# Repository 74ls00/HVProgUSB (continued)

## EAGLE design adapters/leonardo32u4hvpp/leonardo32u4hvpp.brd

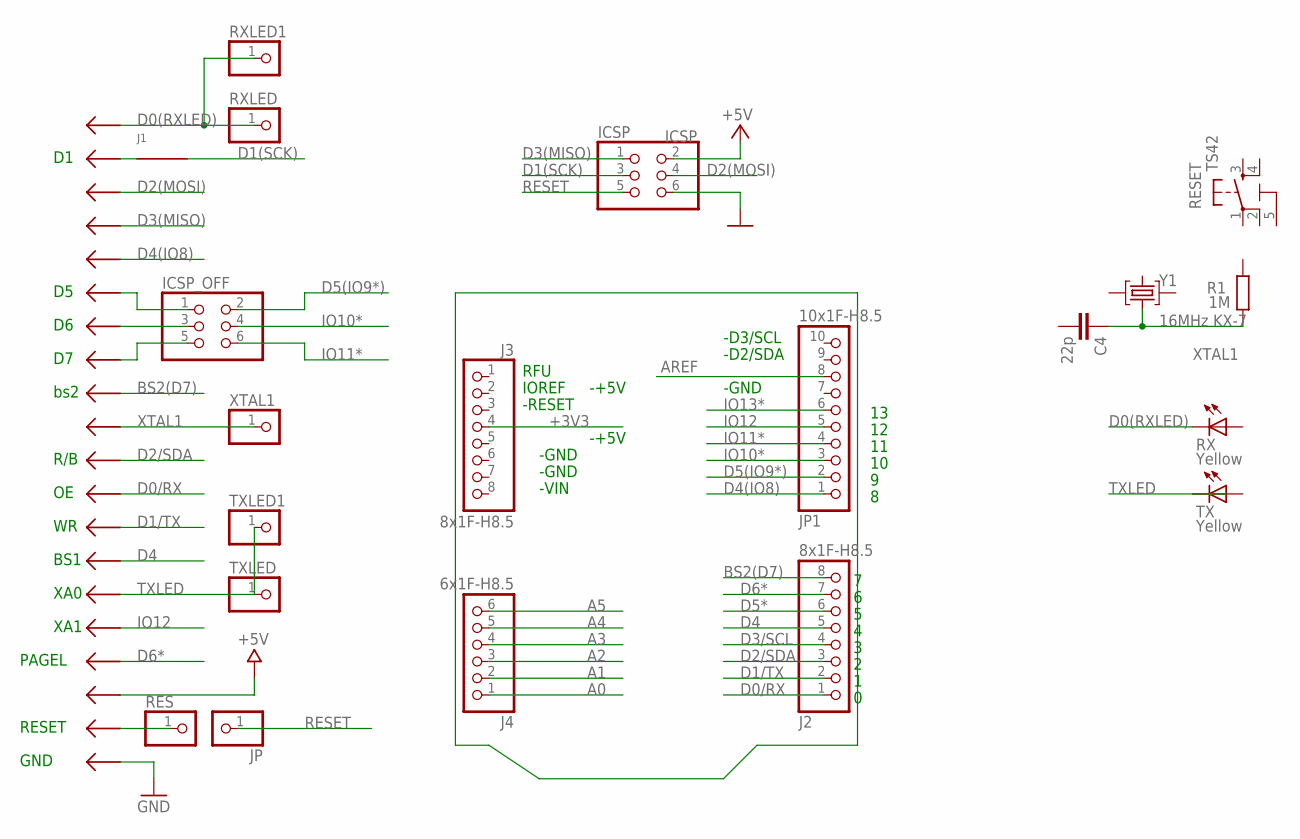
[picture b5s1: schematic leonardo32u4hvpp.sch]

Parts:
C4: 22p; C0603-ROUND
ICSP: ICSP; 2X03
ICSP_OFF: PINHD-2X3; 2X03
J1: J; R1206W
J2, J3: 8x1F-H8.5; 1X08
J4: 6x1F-H8.5; 1X06
JP: PINHD-1X1; 1X01
JP1: 10x1F-H8.5; 1X10
R1: 1M; R0603-ROUND
RES: PINHD-1X1; 1X01
RESET: TS42
RX: Yellow; CHIPLED_0805
RXLED, RXLED1: PINHD-1X1; 1X01
TX: Yellow; CHIPLED_0805
TXLED, TXLED1: PINHD-1X1; 1X01
U$2: PROGRAMMER_P_AVR
XTAL1: PINHD-1X1; 1X01
Y1: 16MHz KX-7; CRYSTAL-3.2-2.5

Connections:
5-GND: RESET.5 (5-GND)
+3V3: J3.4
+5V: ICSP.2, U$2.VCC
A0: J4.1
A1: J4.2
A2: J4.3
A3: J4.4
A4: J4.5
A5: J4.6
AREF: JP1.8
BS2(D7): J2.8, U$2.BS2
D0(RXLED): RX.C, RXLED.1, RXLED1.1, U$2.D0
D0/RX: J2.1, U$2.OE
D1(SCK): ICSP.3, J1.1
D1/TX: J2.2, U$2.WR
D2(MOSI): ICSP.4, U$2.D2
D2/SDA: J2.3, U$2.RB
D3(MISO): ICSP.1, U$2.D3
D3/SCL: J2.4
D4: J2.5, U$2.BS1
D4(IO8): JP1.1, U$2.D4
D5(IO9*): ICSP_OFF.2, JP1.2
D5*: J2.6
D6*: J2.7, U$2.PAGEL
GND: ICSP.6, U$2.GND, U$2.GND01 (GND), U$2.GND2 (GND), U$2.GND03 (GND), U$2.GND04 (GND), U$2.GND05 (GND), U$2.GND06 (GND), U$2.GND07 (GND), U$2.GND08 (GND), U$2.GND09 (GND), U$2.GND10 (GND), U$2.GND11 (GND), U$2.GND12 (GND), U$2.GND13 (GND), U$2.GND14 (GND), U$2.GND15 (GND), U$2.GND16 (GND), U$2.GND17 (GND), U$2.GND18 (GND), U$2.GND19 (GND), U$2.GND20 (GND), U$2.GND21 (GND), U$2.GND22 (GND)
IO10*: ICSP_OFF.4, JP1.3
IO11*: ICSP_OFF.6, JP1.4
IO12: JP1.5, U$2.XA1
IO13*: JP1.6
unnamed: J1.2, U$2.D1
unnamed: ICSP_OFF.5, U$2.D7
unnamed: ICSP_OFF.3, U$2.D6
unnamed: ICSP_OFF.1, U$2.D5
unnamed: RES.1, U$2.RESET
RESET: ICSP.5, JP.1
TXLED: TX.C, TXLED.1, TXLED1.1, U$2.XA0
XTAL1: C4.1, R1.1, U$2.XTAL1, XTAL1.1, Y1.1 (C1)

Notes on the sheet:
IOREF
RFU
bs2
R/B
BS1
XA0
XA1
PAGEL
RESET
GND
-D2/SDA
-D3/SCL
-GND
-VIN
-RESET
-+5V

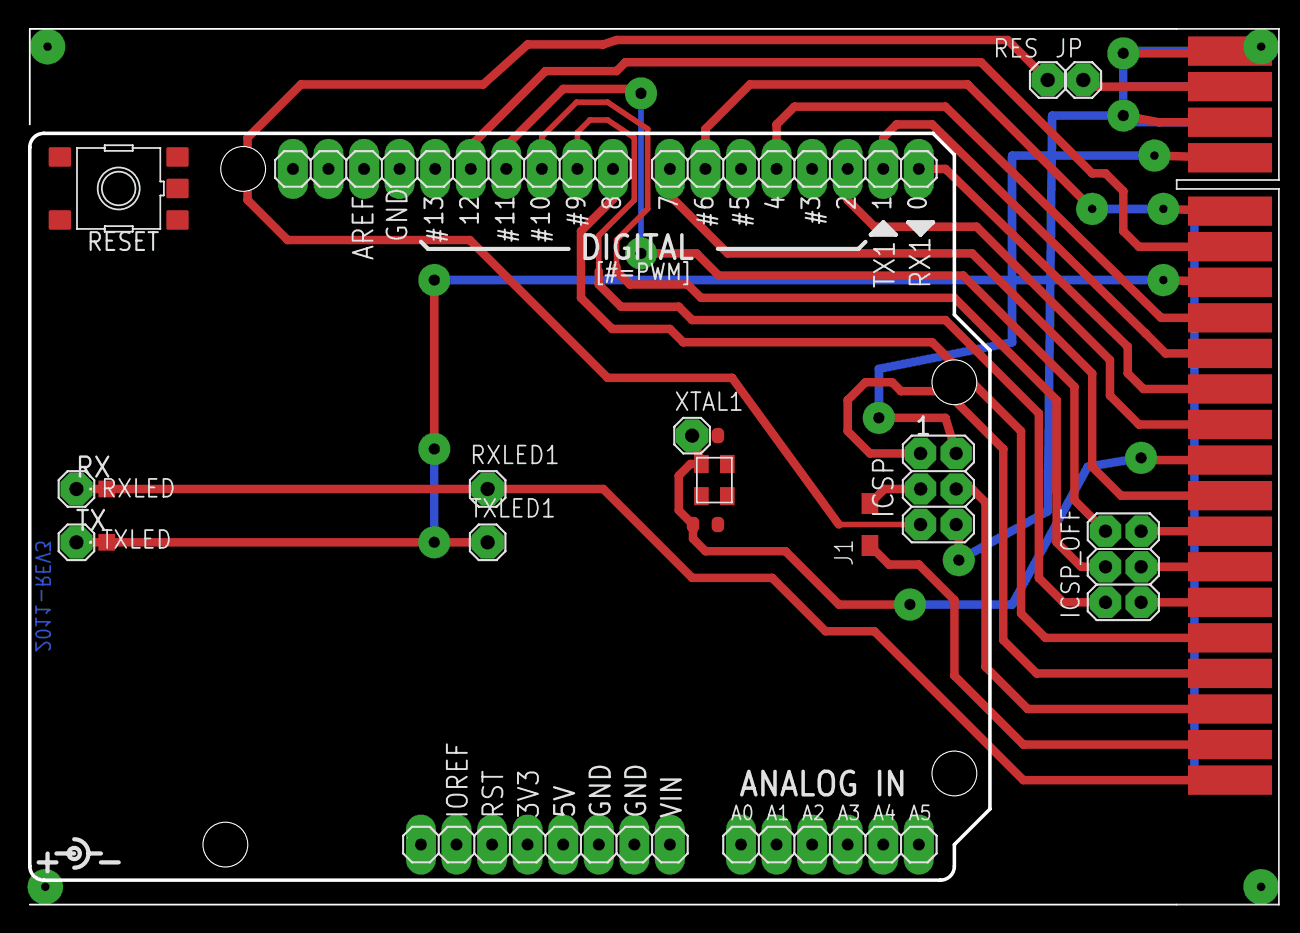
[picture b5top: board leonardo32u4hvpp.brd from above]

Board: 2 copper layers, 68.6 x 53.3 mm, 21 parts (1 on the bottom side), 25 nets.

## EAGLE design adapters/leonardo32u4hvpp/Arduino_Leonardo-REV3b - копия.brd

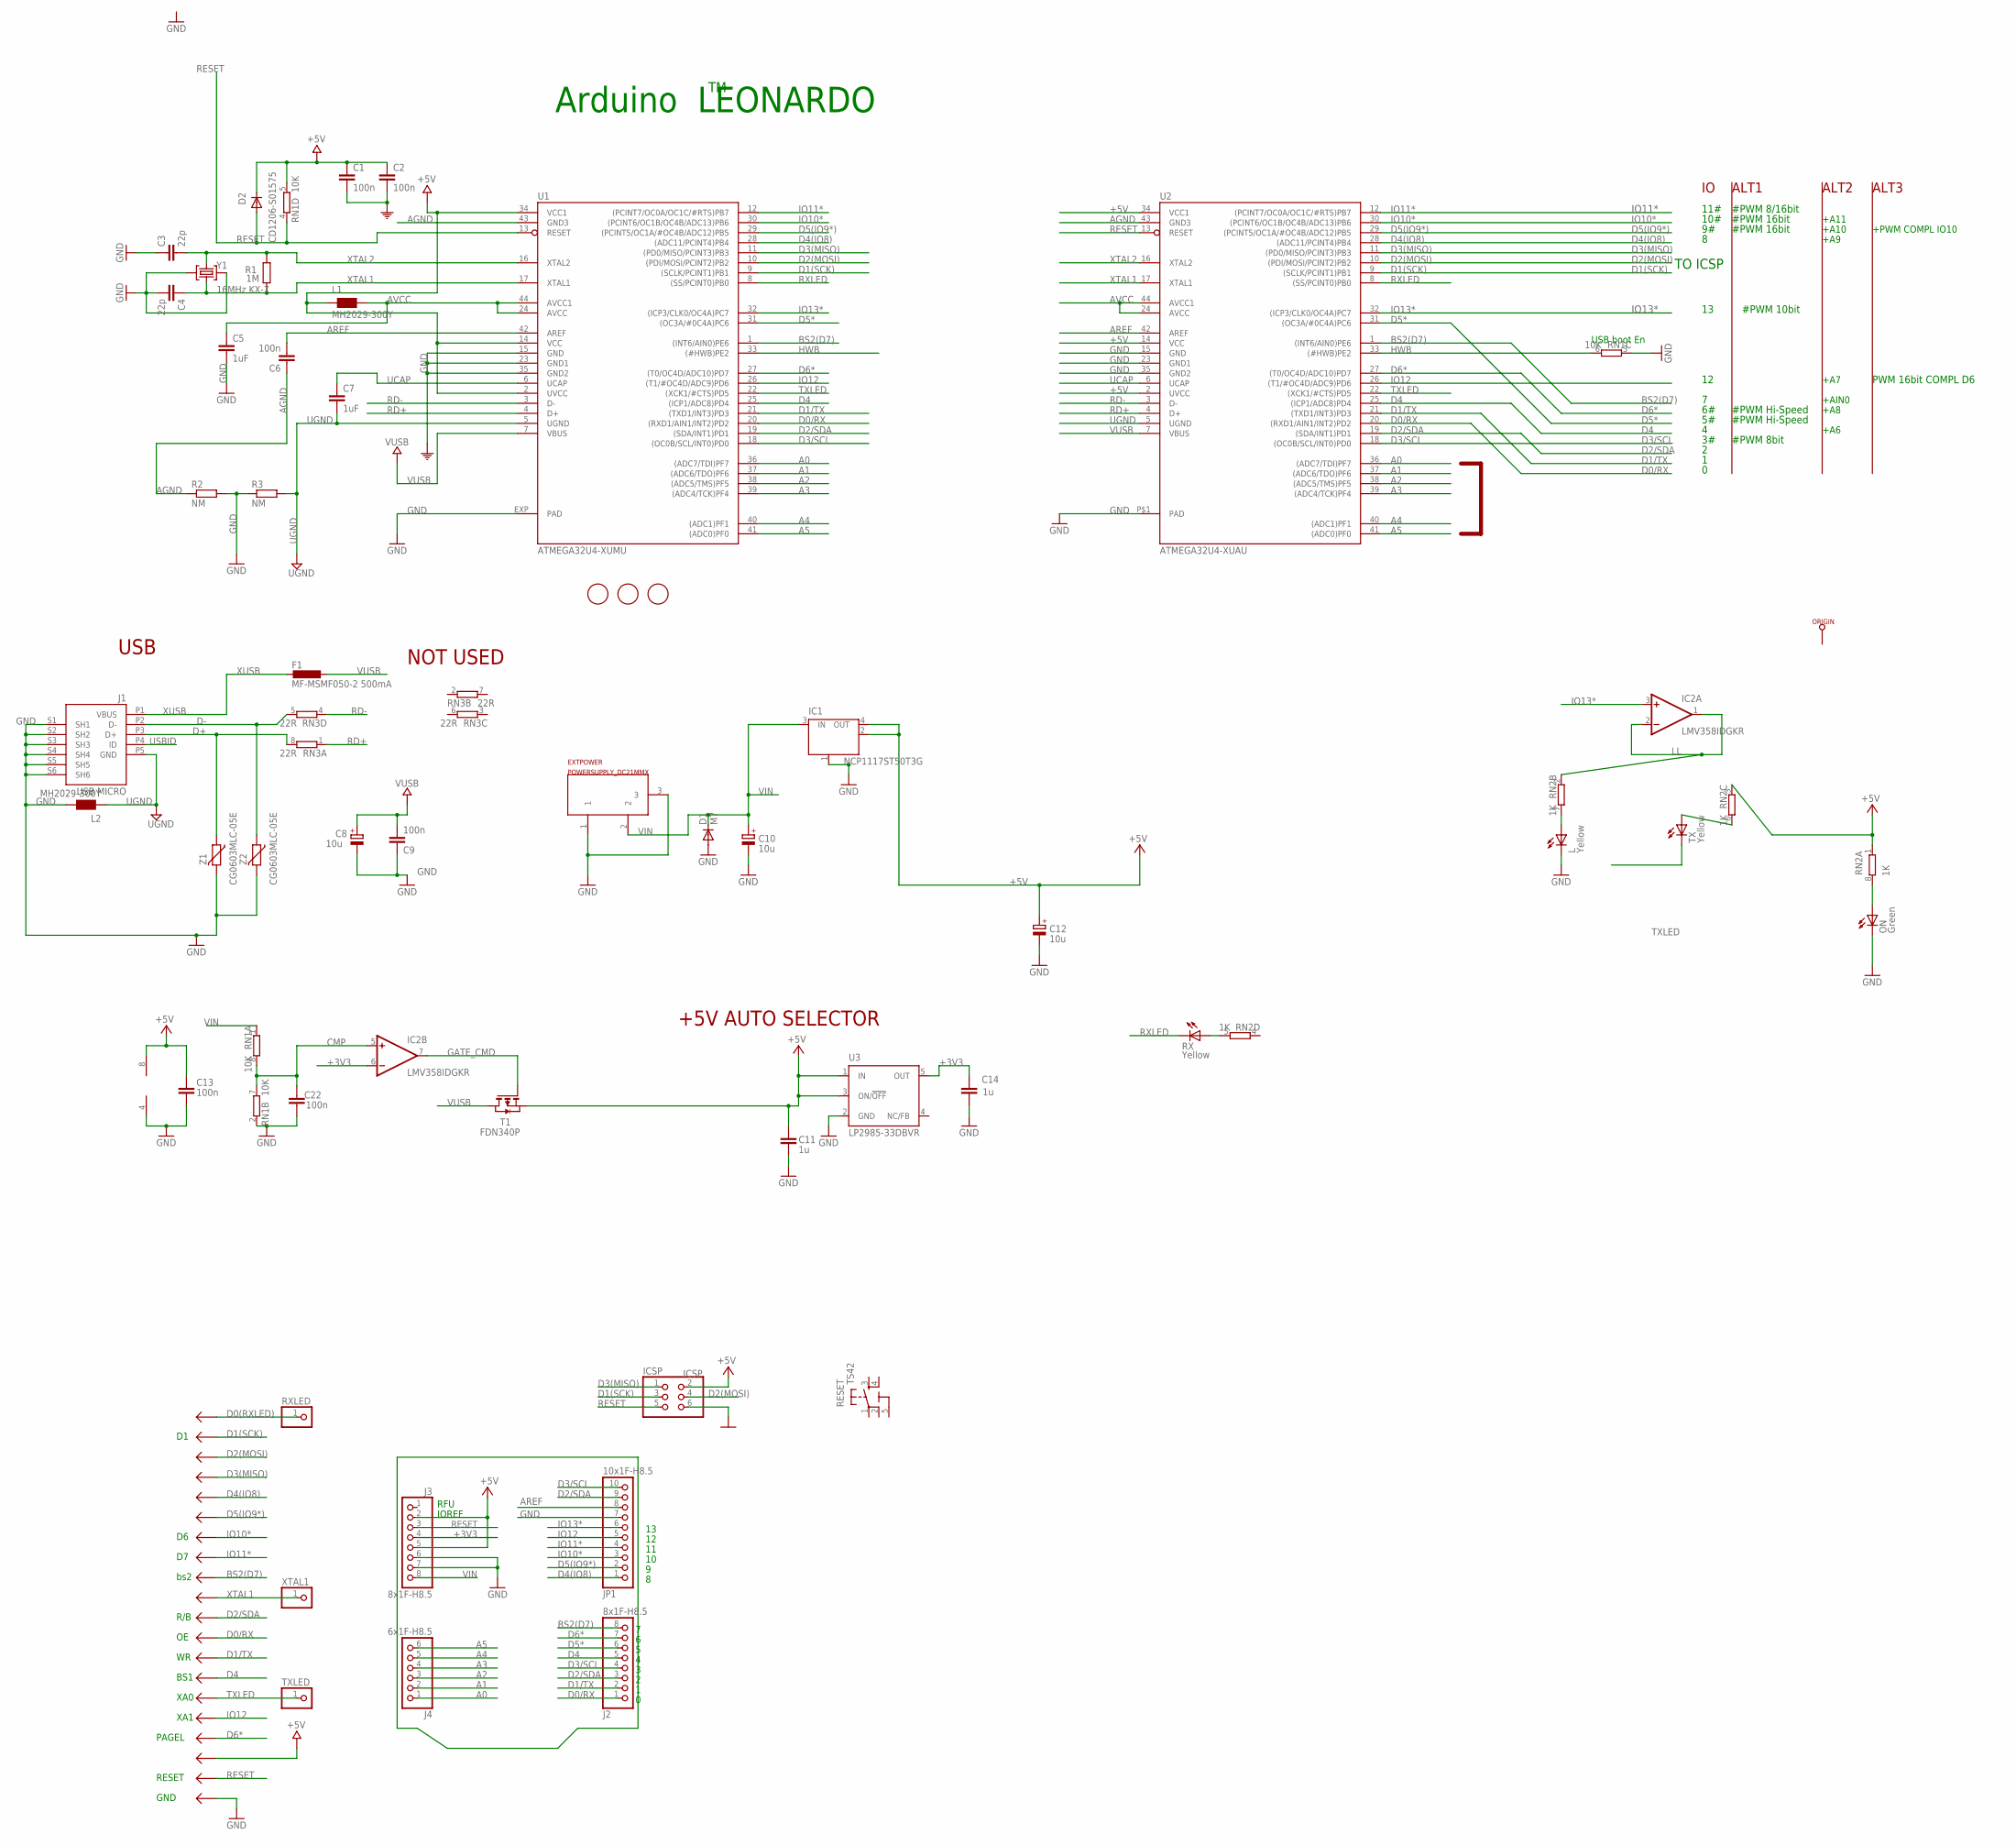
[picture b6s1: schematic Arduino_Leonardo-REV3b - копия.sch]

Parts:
C1, C2, C6, C9, C13, C22: 100n; C0603-ROUND
C3, C4: 22p; C0603-ROUND
C5, C7: 1uF; C0603-ROUND
C8, C10, C12: 10u; SMC_B
C11, C14: 1u; C0603-ROUND
D1: M7; SMB
D2: CD1206-S01575; MINIMELF
EXTPOWER: POWERSUPPLY_DC21MMX; POWERSUPPLY_DC-21MM
F1: MF-MSMF050-2 500mA; L1812
FID1, FID2, FID3: FIDUCIALMOUNT; FIDUCIA-MOUNT
IC1: NCP1117ST50T3G; SOT223
IC2: LMV358IDGKR; MSOP08
ICSP: ICSP; 2X03
J1: USB MICRO; CON2_USB_MICRO_B_AT
J2, J3: 8x1F-H8.5; 1X08
J4: 6x1F-H8.5; 1X06
JP1: 10x1F-H8.5; 1X10
L: Yellow; CHIPLED_0805
L1, L2: MH2029-300Y; 0805
ON: Green; CHIPLED_0805
ORIGIN: TP_SP; TP-SP
R1: 1M; R0603-ROUND
R2, R3: NM; R0402
RESET: TS42
RN1: 10K; CAY16
RN2: 1K; CAY16
RN3: 22R; CAY16
RX: Yellow; CHIPLED_0805
RXLED: PINHD-1X1; 1X01
T1: FDN340P; SOT-23
TX: Yellow; CHIPLED_0805
TXLED: PINHD-1X1; 1X01
U1: ATMEGA32U4-XUMU; QFN44ML7X7
U2: ATMEGA32U4-XUAU; TQFP44-PAD
U3: LP2985-33DBVR; SOT23-DBV
U$2: PROGRAMMER_P_AVR
XTAL1: PINHD-1X1; 1X01
Y1: 16MHz KX-7; CRYSTAL-3.2-2.5
Z1, Z2: CG0603MLC-05E; CT/CN0603

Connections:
5-GND: RESET.5 (5-GND)
+3V3: C14.2, IC2.6 (-IN), J3.4, U3.5 (OUT)
+5V: C1.1, C2.1, C11.2, C12.+, C13.1, D2.C, IC1.2 (OUT), IC1.4 (OUT), IC2.8 (V+), ICSP.2, J3.2, J3.5, L1.1, RN1.5 (2), RN2.1, RN2.3 (1), T1.2 (S), U1.2 (UVCC), U1.14 (VCC), U1.34 (VCC1), U2.2 (UVCC), U2.14 (VCC), U2.34 (VCC1), U3.1 (IN), U3.3 (ON/!OFF), U$2.VCC
A0: J4.1, U1.36 ((ADC7/TDI)PF7), U2.36 ((ADC7/TDI)PF7)
A1: J4.2, U1.37 ((ADC6/TDO)PF6), U2.37 ((ADC6/TDO)PF6)
A2: J4.3, U1.38 ((ADC5/TMS)PF5), U2.38 ((ADC5/TMS)PF5)
A3: J4.4, U1.39 ((ADC4/TCK)PF4), U2.39 ((ADC4/TCK)PF4)
A4: J4.5, U1.40 ((ADC1)PF1), U2.40 ((ADC1)PF1)
A5: J4.6, U1.41 ((ADC0)PF0), U2.41 ((ADC0)PF0)
AGND: C6.1, R2.1, U1.43 (GND3), U2.43 (GND3)
AREF: C6.2, JP1.8, U1.42 (AREF), U2.42 (AREF)
AVCC: C5.1, L1.2, U1.24 (AVCC), U1.44 (AVCC1), U2.24 (AVCC), U2.44 (AVCC1)
BS2(D7): J2.8, U1.1 ((INT6/AIN0)PE6), U2.1 ((INT6/AIN0)PE6), U$2.BS2
CMP: C22.2, IC2.5 (+IN), RN1.7 (2), RN1.8 (2)
D0(RXLED): RXLED.1, U$2.D0
D0/RX: J2.1, U1.20 ((RXD1/AIN1/INT2)PD2), U2.20 ((RXD1/AIN1/INT2)PD2), U$2.OE
D1(SCK): ICSP.3, U1.9 ((SCLK/PCINT1)PB1), U2.9 ((SCLK/PCINT1)PB1), U$2.D1
D1/TX: J2.2, U1.21 ((TXD1/INT3)PD3), U2.21 ((TXD1/INT3)PD3), U$2.WR
D2(MOSI): ICSP.4, U1.10 ((PDI/MOSI/PCINT2)PB2), U2.10 ((PDI/MOSI/PCINT2)PB2), U$2.D2
D2/SDA: J2.3, JP1.9, U1.19 ((SDA/INT1)PD1), U2.19 ((SDA/INT1)PD1), U$2.RB
D3(MISO): ICSP.1, U1.11 ((PD0/MISO/PCINT3)PB3), U2.11 ((PD0/MISO/PCINT3)PB3), U$2.D3
D3/SCL: J2.4, JP1.10, U1.18 ((OC0B/SCL/INT0)PD0), U2.18 ((OC0B/SCL/INT0)PD0)
D4: J2.5, U1.25 ((ICP1/ADC8)PD4), U2.25 ((ICP1/ADC8)PD4), U$2.BS1
D4(IO8): JP1.1, U1.28 ((ADC11/PCINT4)PB4), U2.28 ((ADC11/PCINT4)PB4), U$2.D4
D5(IO9*): JP1.2, U1.29 ((PCINT5/OC1A/#OC4B/ADC12)PB5), U2.29 ((PCINT5/OC1A/#OC4B/ADC12)PB5), U$2.D5
D5*: J2.6, U1.31 ((OC3A/#0C4A)PC6), U2.31 ((OC3A/#0C4A)PC6)
D6*: J2.7, U1.27 ((T0/OC4D/ADC10)PD7), U2.27 ((T0/OC4D/ADC10)PD7), U$2.PAGEL
D+: J1.P3 (D+), RN3.8 (2), Z1.1
D-: J1.P2 (D-), RN3.5 (2), Z2.1
GATE_CMD: IC2.7 (OUT), T1.3 (G)
GND: C1.2, C2.2, C3.1, C4.2, C5.2, C8.-, C9.1, C10.-, C11.1, C12.-, C13.2, C14.1, C22.1, D1.A, EXTPOWER.1, EXTPOWER.3, IC1.1 (GND/ADJ), IC2.4 (V-), ICSP.6, J1.S1 (SH1), J1.S2 (SH2), J1.S3 (SH3), J1.S4 (SH4), J1.S5 (SH5), J1.S6 (SH6), J3.6, J3.7, JP1.7, L.C, L2.2, ON.C, R2.2, R3.1, RN1.2 (1), RN1.3 (1), U1.15 (GND), U1.23 (GND1), U1.35 (GND2), U1.EXP (PAD), U2.15 (GND), U2.23 (GND1), U2.35 (GND2), U2.P$1 (PAD), U3.2 (GND), U$2.GND, U$2.GND01 (GND), U$2.GND2 (GND), U$2.GND03 (GND), U$2.GND04 (GND), U$2.GND05 (GND), U$2.GND06 (GND), U$2.GND07 (GND), U$2.GND08 (GND), U$2.GND09 (GND), U$2.GND10 (GND), U$2.GND11 (GND), U$2.GND12 (GND), U$2.GND13 (GND), U$2.GND14 (GND), U$2.GND15 (GND), U$2.GND16 (GND), U$2.GND17 (GND), U$2.GND18 (GND), U$2.GND19 (GND), U$2.GND20 (GND), U$2.GND21 (GND), U$2.GND22 (GND), Y1.2 (GND), Y1.4 (GND), Z1.2, Z2.2
HWB: RN1.6 (2), U1.33 ((#HWB)PE2), U2.33 ((#HWB)PE2)
IO10*: JP1.3, U1.30 ((PCINT6/OC1B/OC4B/ADC13)PB6), U2.30 ((PCINT6/OC1B/OC4B/ADC13)PB6), U$2.D6
IO11*: JP1.4, U1.12 ((PCINT7/OC0A/OC1C/#RTS)PB7), U2.12 ((PCINT7/OC0A/OC1C/#RTS)PB7), U$2.D7
IO12: JP1.5, U1.26 ((T1/#OC4D/ADC9)PD6), U2.26 ((T1/#OC4D/ADC9)PD6), U$2.XA1
IO13*: IC2.3 (+IN), JP1.6, U1.32 ((ICP3/CLK0/OC4A)PC7), U2.32 ((ICP3/CLK0/OC4A)PC7)
LL: IC2.1 (OUT), IC2.2 (-IN), RN2.2 (1)
unnamed: L.A, RN2.7 (2)
unnamed: ON.A, RN2.8 (2)
unnamed: RN2.6 (2), TX.A
unnamed: RN2.5 (2), RX.A
RD+: RN3.1, U1.4 (D+), U2.4 (D+)
RD-: RN3.4 (1), U1.3 (D-), U2.3 (D-)
RESET: D2.A, ICSP.5, J3.3, RN1.4 (1), U1.13 (RESET), U2.13 (RESET), U$2.RESET
RXLED: RX.C, U1.8 ((SS/PCINT0)PB0), U2.8 ((SS/PCINT0)PB0)
TXLED: TX.C, TXLED.1, U1.22 ((XCK1/#CTS)PD5), U2.22 ((XCK1/#CTS)PD5), U$2.XA0
UCAP: C7.1, U1.6 (UCAP), U2.6 (UCAP)
UGND: C7.2, J1.P5 (GND), L2.1, R3.2, U1.5 (UGND), U2.5 (UGND)
USBID: J1.P4 (ID)
VIN: C10.+, D1.C, EXTPOWER.2, IC1.3 (IN), J3.8, RN1.1
VUSB: C8.+, C9.2, F1.1, T1.1 (D), U1.7 (VBUS), U2.7 (VBUS)
XTAL1: C4.1, R1.1, U1.17 (XTAL1), U2.17 (XTAL1), U$2.XTAL1, XTAL1.1, Y1.1 (C1)
XTAL2: C3.2, R1.2, U1.16 (XTAL2), U2.16 (XTAL2), Y1.3 (C2)
XUSB: F1.2, J1.P1 (VBUS)

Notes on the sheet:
Arduino LEONARDO
USB boot En
USB
+5V AUTO SELECTOR
NOT USED
TO ICSP
10#
11#
#PWM 8bit
#PWM Hi-Speed
#PWM 8/16bit
#PWM 16bit
PWM 16bit COMPL D6
#PWM 10bit
+A6
+A7
IOREF
RFU
+A11
+A10
+A8
+A9
+PWM COMPL IO10
+AIN0
ALT1
ALT2
ALT3
bs2
R/B
BS1
XA0
XA1
PAGEL
RESET
GND

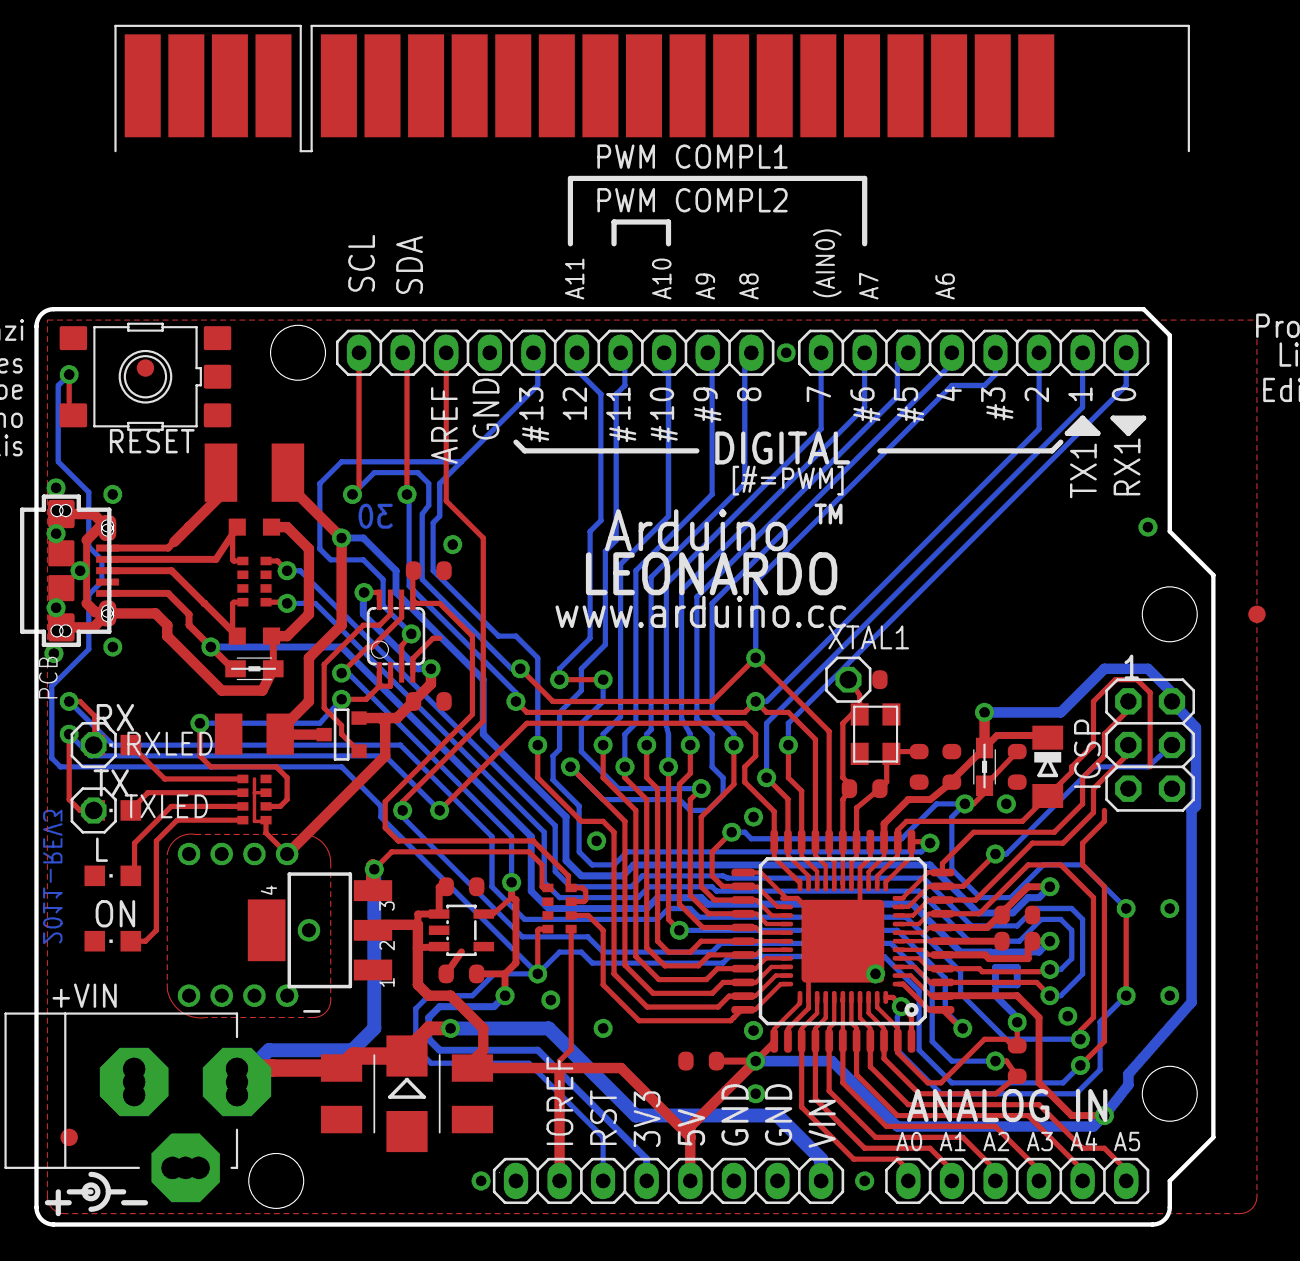
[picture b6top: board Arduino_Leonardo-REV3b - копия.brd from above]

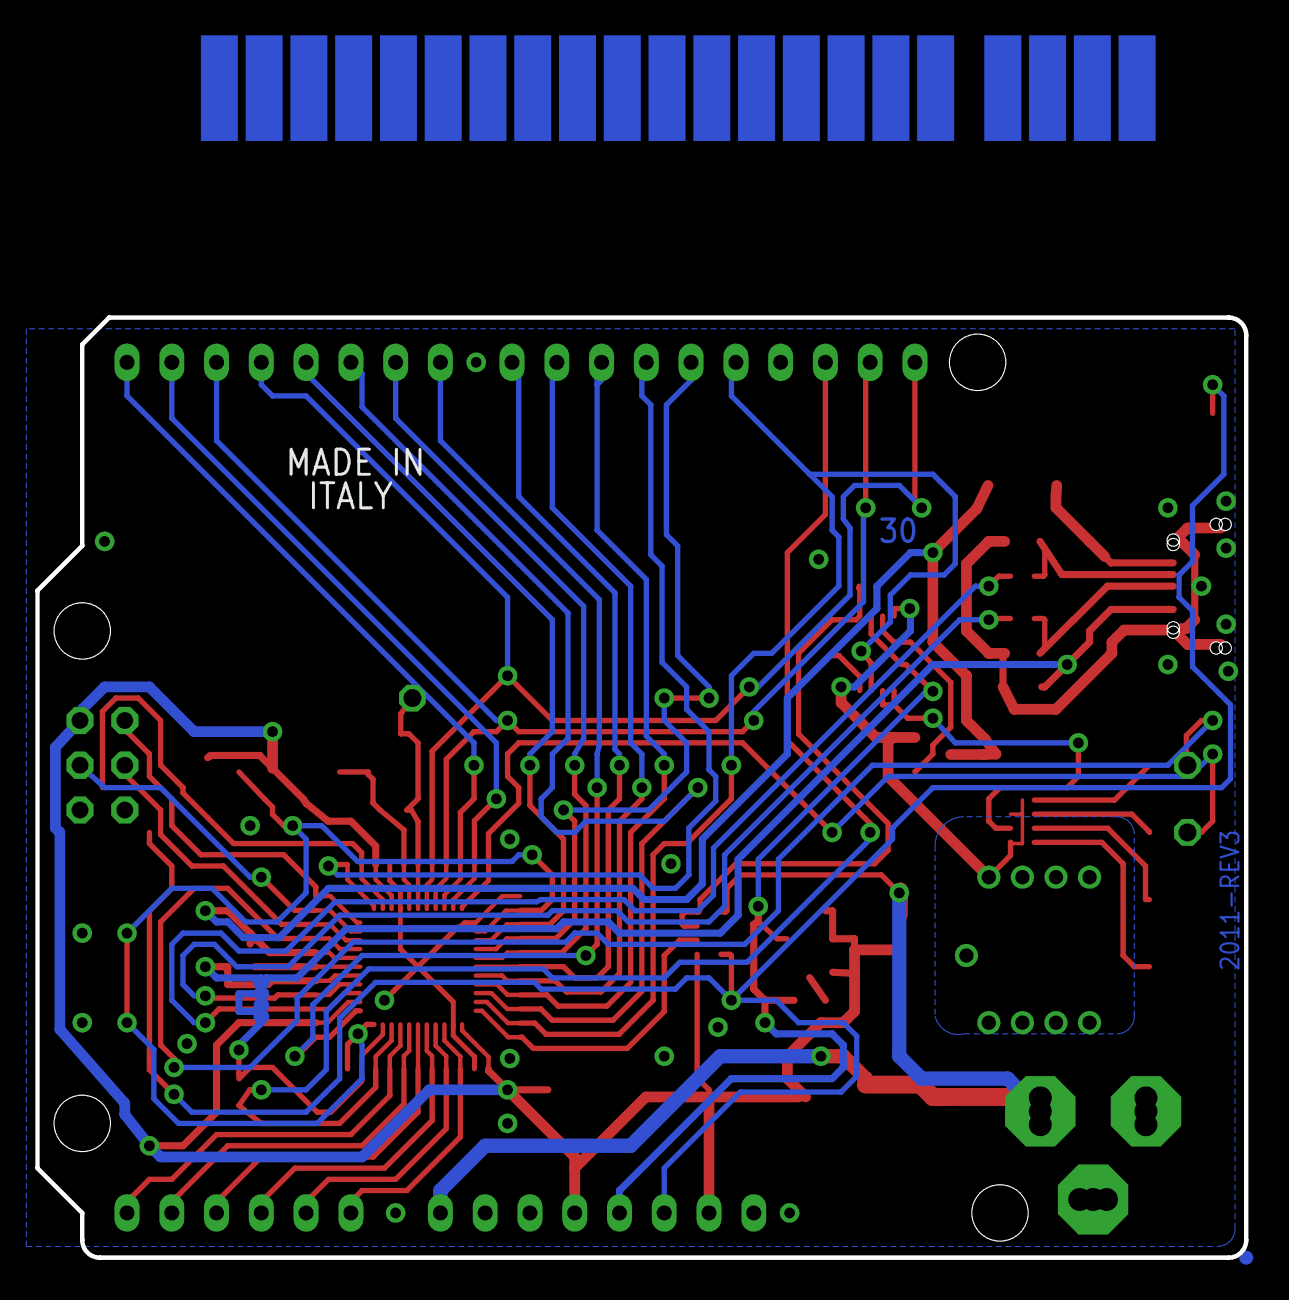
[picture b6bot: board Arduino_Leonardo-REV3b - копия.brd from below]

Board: 2 copper layers, 68.6 x 53.3 mm, 55 parts (2 on the bottom side), 52 nets.

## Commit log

2016-08-26 t32u4
2018-10-19 add 3v3 led ..
2018-11-23 add doc panel
2018-11-27 qfp48 adapter
2018-11-30 rename adapter
2018-12-02 rename
2018-12-02 add readme8
